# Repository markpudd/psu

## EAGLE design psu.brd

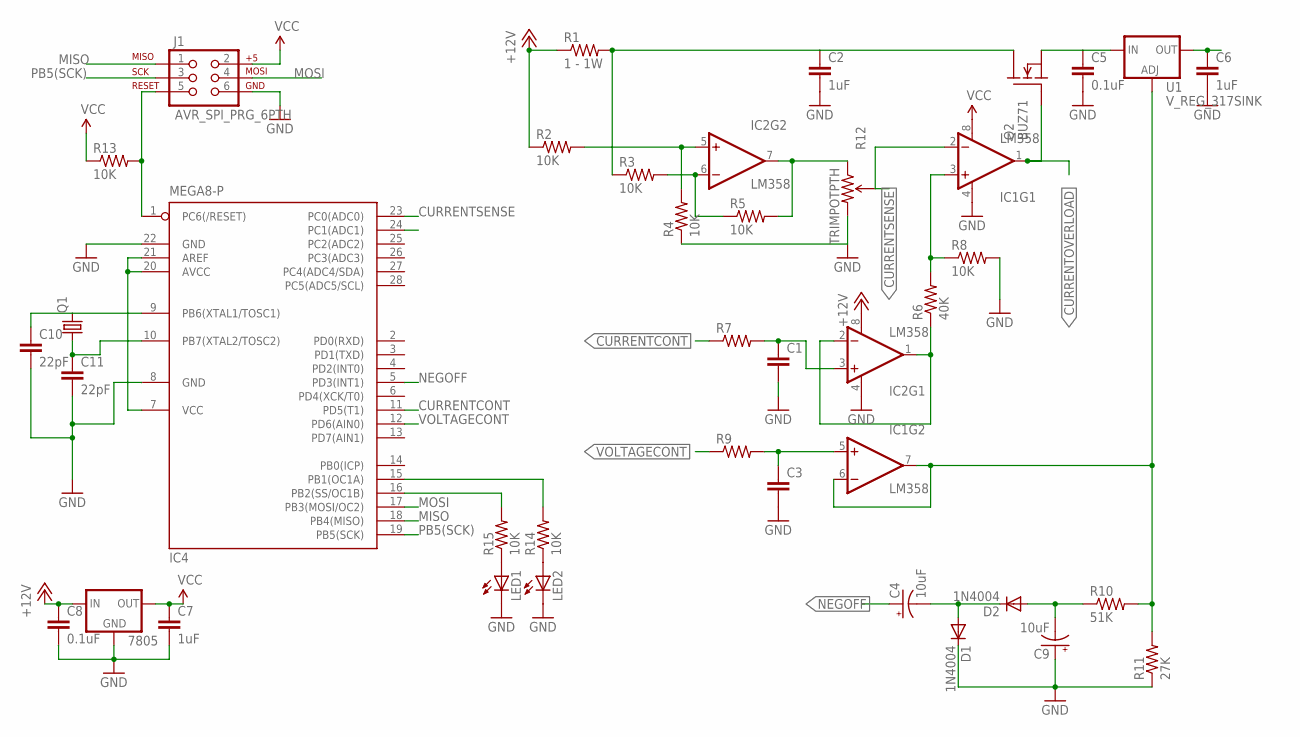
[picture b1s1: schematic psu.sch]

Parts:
7805: V_REG_78XXSINK; TO220-IGO
C1, C3: CAPPTH; CAP-PTH-SMALL
C2, C6, C7: 1uF; CAP-PTH-SMALL
C4, C9: 10uF; CPOL-RADIAL-10UF-25V
C5, C8: 0.1uF; CAP-PTH-SMALL
C10, C11: 22pF; 0805
D1, D2: 1N4004; DO41-10
IC1, IC2: LM358; DIP08
IC4: MEGA8-P; DIL28-3
J1: AVR_SPI_PRG_6PTH; 2X3
LED1, LED2: LED5MM
Q1: CRYSTALHC49UP; HC49UP
Q2: BUZ71; TO220
R1: 1 - 1W; AXIAL-0.4
R2, R3, R4, R5, R8, R14, R15: 10K; AXIAL-0.4
R6: 40K; AXIAL-0.4
R7, R9: RESISTORPTH-1/4W; AXIAL-0.4
R10: 51K; AXIAL-0.4
R11: 27K; AXIAL-0.4
R12: TRIMPOTPTH; TRIM_POT_PTH
R13: 10K; 0805
U1: V_REG_317SINK; TO220-ADJ

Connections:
+12V: 7805.IN, C8.1, IC2.8 (V+), R1.P$1 (1), R2.P$1 (1)
COUT: IC2.7 (OUT), R5.P$2 (2), R12.1 (CCW)
CURRENTCONT: IC4.11 (PD5(T1)), R7.P$1 (1)
CURRENTOVERLOAD: IC1.1 (OUT), IC4.24 (PC1(ADC1)), Q2.1 (G)
CURRENTSENSE: IC1.2 (-IN), IC4.23 (PC0(ADC0)), R12.2 (WIPER)
GND: 7805.GND, C1.2, C2.2, C3.2, C5.2, C6.2, C7.2, C8.2, C9.1 (+), C10.2, C11.2, D1.C, IC1.4 (V-), IC2.4 (V-), IC4.8 (GND), IC4.22 (GND), J1.6, LED1.K (C), LED2.K (C), R4.P$1 (1), R8.P$2 (2), R11.P$1 (1), R12.3 (CW)
MISO: IC4.18 (PB4(MISO)), J1.1
MOSI: IC4.17 (PB3(MOSI/OC2)), J1.4
unnamed: IC2.6 (-IN), R3.P$2 (2), R5.P$1 (1)
unnamed: IC1.3 (+IN), R6.P$2 (2), R8.P$1 (1)
unnamed: IC2.5 (+IN), R2.P$2 (2), R4.P$2 (2)
unnamed: IC2.1 (OUT), IC2.2 (-IN), R6.P$1 (1)
unnamed: IC1.6 (-IN), IC1.7 (OUT), R10.P$2 (2), R11.P$2 (2), U1.ADJ
unnamed: C4.2 (-), D1.A, D2.C
unnamed: C6.1, U1.OUT
unnamed: C10.1, IC4.9 (PB6(XTAL1/TOSC1)), Q1.2
unnamed: C2.1, Q2.2 (D), R1.P$2 (2), R3.P$1 (1)
unnamed: IC4.15 (PB1(OC1A)), R14.P$2 (2)
unnamed: C11.1, IC4.10 (PB7(XTAL2/TOSC2)), Q1.1
unnamed: IC4.7 (VCC), IC4.20 (AVCC), IC4.21 (AREF)
unnamed: C3.1, IC1.5 (+IN), R9.P$2 (2)
unnamed: IC4.1 (PC6(/RESET)), J1.5, R13.2
unnamed: C9.2 (-), D2.A, R10.P$1 (1)
unnamed: C1.1, IC2.3 (+IN), R7.P$2 (2)
unnamed: IC4.16 (PB2(SS/OC1B)), R15.P$2 (2)
unnamed: LED1.A, R15.P$1 (1)
unnamed: LED2.A, R14.P$1 (1)
unnamed: C5.1, Q2.3 (S), U1.IN
NEGOFF: C4.1 (+), IC4.5 (PD3(INT1))
PB5(SCK): IC4.19 (PB5(SCK)), J1.3
VCC: 7805.OUT, C7.1, IC1.8 (V+), J1.2, R13.1
VOLTAGECONT: IC4.12 (PD6(AIN0)), R9.P$1 (1)

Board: 2 copper layers, 38 parts (0 on the bottom side), 32 nets, no tracks yet.

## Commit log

2014-12-28 Initail Version

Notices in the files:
parts and their libraries:
SparkFun-AnalogIC: Licensing: CC v3.0 Share-Alike You are welcome to use this library for commercial purposes.
